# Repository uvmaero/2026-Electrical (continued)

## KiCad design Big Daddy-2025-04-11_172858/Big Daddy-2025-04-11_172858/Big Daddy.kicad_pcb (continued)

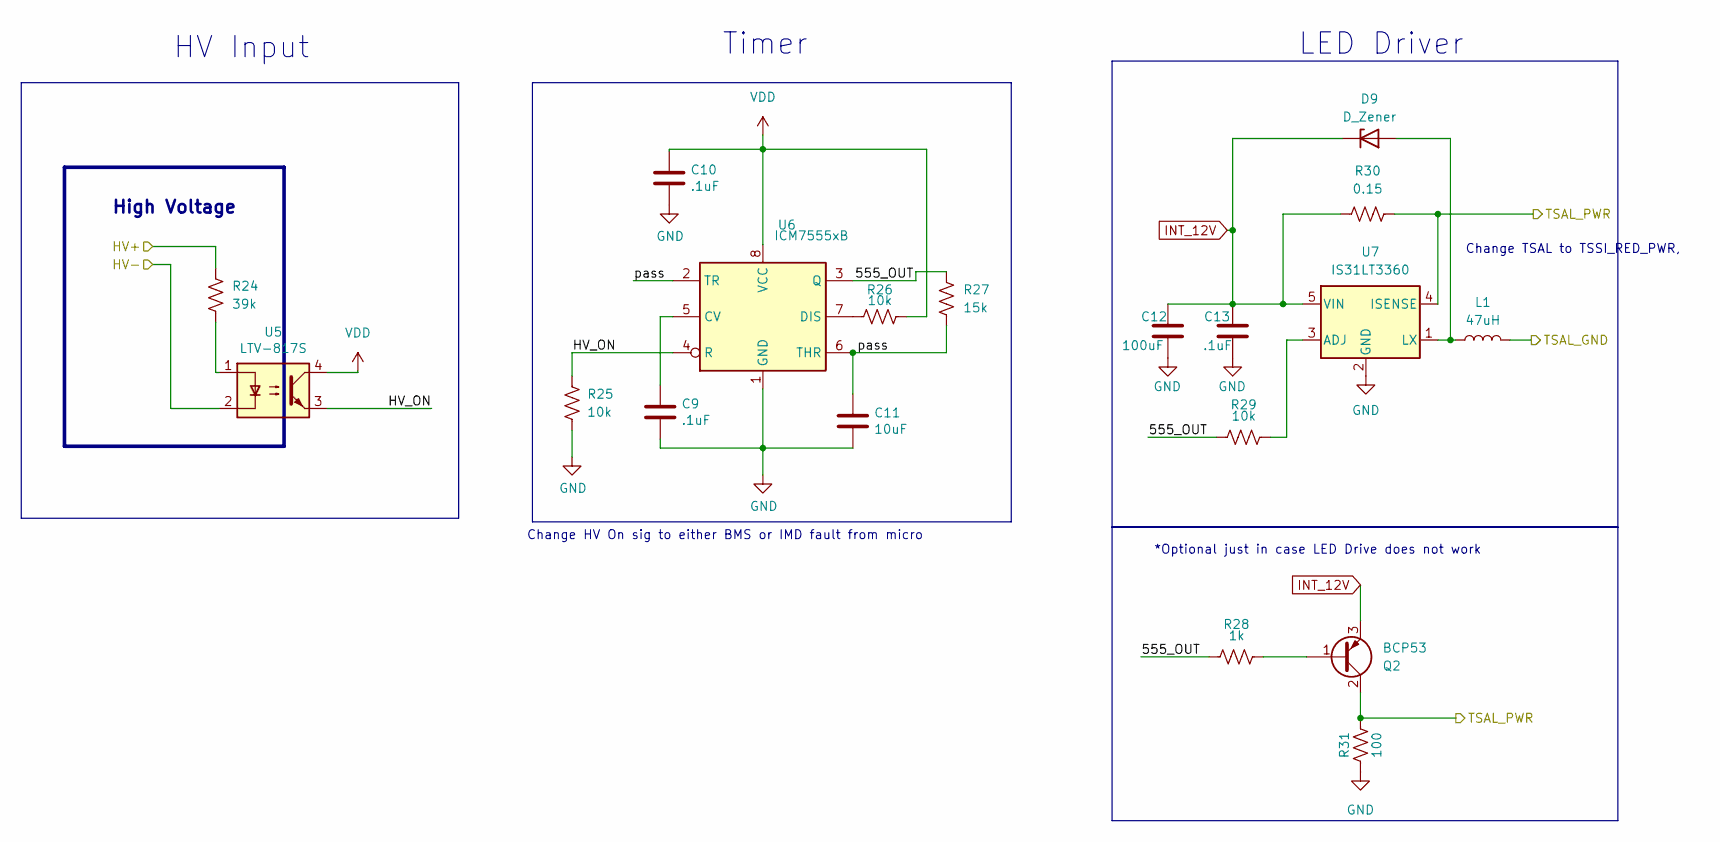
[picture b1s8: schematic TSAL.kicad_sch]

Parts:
C9, C10, C13: .1uF; C_0603_1608Metric_Pad1.08x0.95mm_HandSolder; Manufacturer_Part_Number CC0603KRX7R7BB104; Digikey part number 311-1088-1-ND
C11: 10uF; C_0603_1608Metric_Pad1.08x0.95mm_HandSolder; Manufacturer_Part_Number CL10A106KQ8NNNC; Digikey part number 1276-1038-1-ND
C12: 100uF; CP_Radial_D10.0mm_P5.00mm
D9: D_Zener; D_SOD-123; Manufacturer_Part_Number MMSZ5231B-7-F; Digikey part number MMSZ5231B-FDICT-ND
L1: 47uH; L_0603_1608Metric_Pad1.05x0.95mm_HandSolder; Manufacturer_Part_Number LBMF1608T470K; Digikey part number 587-1716-1-ND
Q2: BCP53; SOT-223-3_TabPin2; Manufacturer_Part_Number BCP53; Digikey part number BCP53FSCT-ND
R24: 39k; R_Axial_DIN0414_L11.9mm_D4.5mm_P15.24mm_Horizontal; Manufacturer_Part_Number CF12JT39K0; Digikey part number CF12JT39K0CT-ND
R25, R26, R29: 10k; R_0603_1608Metric_Pad0.98x0.95mm_HandSolder; Manufacturer_Part_Number RK73H1JTTD1002F; Digikey part number 2019-RK73H1JTTD1002FCT-ND
R27: 15k; R_0603_1608Metric_Pad0.98x0.95mm_HandSolder; Manufacturer_Part_Number ERA-3AEB153V; Digikey part number P15KDBCT-ND
R28: 1k; R_0603_1608Metric_Pad0.98x0.95mm_HandSolder; Manufacturer_Part_Number RMCF0603FT1K00; Digikey part number RMCF0603FT1K00CT-ND
R30: 0.15; R_0603_1608Metric_Pad0.98x0.95mm_HandSolder; Manufacturer_Part_Number RL0603FR-070R15L; Digikey part number 311-.15QCT-ND
R31: 100; R_1206_3216Metric_Pad1.30x1.75mm_HandSolder; Manufacturer_Part_Number ERJ-8ENF1000V; Digikey part number P100FCT-ND
U5: LTV-817S; SMDIP-4_W9.53mm; Manufacturer_Part_Number LTV-817S; Digikey part number 160-1367-5-ND
U6: ICM7555xB; SOIC-8_3.9x4.9mm_P1.27mm; Manufacturer_Part_Number ICM7555CBAZ-T; Digikey part number ICM7555CBAZ-TCT-ND
U7: IS31LT3360; SOT-89-5; Manufacturer_Part_Number IS31LT3360-SDLS4-TR; Digikey part number 2521-IS31LT3360-SDLS4-TRCT-ND

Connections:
/Connectors/TSAL_GND: L1.2; also elsewhere on the board
/Connectors/TSAL_PWR: Q2.2 (C), Q2.4 (C), R30.2, R31.2, U7.4 (ISENSE); also elsewhere on the board
/High Voltage/TSAL/555_OUT: R27.1, R28.1, R29.1, U6.3 (Q)
/High Voltage/TSAL/HV+: R24.1; also elsewhere on the board
/High Voltage/TSAL/HV-: U5.2; also elsewhere on the board
/High Voltage/TSAL/HV_ON: R25.1, U5.3, U6.4 (R)
/High Voltage/TSAL/pass: C11.1, R27.2, U6.2 (TR), U6.6 (THR)
GND: C9.2, C10.2, C11.2, C12.1, C13.1, R25.2, R31.1, U6.1 (GND), U7.2 (GND); also elsewhere on the board
INT_12V: C12.2, C13.2, D9.1 (K), Q2.3 (E), R30.1, U7.5 (VIN); also elsewhere on the board
unnamed: D9.2 (A), L1.1, U7.1 (LX)
unnamed: Q2.1 (B), R28.2
unnamed: R24.2, U5.1
unnamed: C9.1, U6.5 (CV)
unnamed: R26.1, U6.7 (DIS)
unnamed: R29.2, U7.3 (ADJ)
VDD: C10.1, R26.2, U5.4, U6.8 (VCC); also elsewhere on the board

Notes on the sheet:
Change HV On sig to either BMS or IMD fault from micro
*Optional just in case LED Drive does not work
LED Driver
High Voltage
HV Input
Timer
Change TSAL to TSSI_RED_PWR,

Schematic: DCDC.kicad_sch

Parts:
C14, C15: 0.68uF; C_Rect_L18.0mm_W8.0mm_P15.00mm_FKS3_FKP3
C16, C17: 4700uF; C_Radial_D18.0mm_H35.5mm_P7.50mm
L2: 1uH; L_1008_2520Metric_Pad1.43x2.20mm_HandSolder; Manufacturer_Part_Number LQM2HPN1R0MG0L; Digikey part number 490-5112-1-ND
L3: 0.15uH; L_0805_2012Metric_Pad1.15x1.40mm_HandSolder; Manufacturer_Part_Number CE201210-R15J; Digikey part number CE201210-R15JCT-ND
R35, R40: 1; R_2512_6332Metric_Pad1.40x3.35mm_HandSolder; Manufacturer_Part_Number RK73H1JTTD1002F; Digikey part number 2019-RK73H1JTTD1002FCT-ND
R36: 300; R_0603_1608Metric_Pad0.98x0.95mm_HandSolder; Manufacturer_Part_Number ERJ-3GEYJ301V; Digikey part number P300GCT-ND
R37, R38, R39: 1k; R_0603_1608Metric_Pad0.98x0.95mm_HandSolder; Manufacturer_Part_Number RMCF0603FT1K00; Digikey part number RMCF0603FT1K00CT-ND
RV1: 50k TC33x-2-503E; Potentiometer_Bourns_TC33X_Vertical; Manufacturer_Part_Number TC33X-2-503E; Digikey part number TC33X-503ECT-ND
U8: Vicor_AERO; vicor-socket-no-cutouts
U9: LTV-817S; SMDIP-4_W9.53mm; Manufacturer_Part_Number LTV-817S; Digikey part number 160-1367-5-ND
U10: TLP184; MFSOP6-4_4.4x3.6mm_P1.27mm; Manufacturer_Part_Number TLP184(BL-TPL,SE; Digikey part number TLP184(BL-TPLSECT-ND

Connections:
/Fusing/Vicor_In: C17.1, L3.2, R40.1; also elsewhere on the board
/High Voltage/DCDC/EN_HV: U8.3 (EN), U9.4
/High Voltage/DCDC/FAULT_HV: R37.2, U8.4 (FT)
/High Voltage/DCDC/HV+: L2.1, R35.2; also elsewhere on the board
/High Voltage/DCDC/HV-: C14.2, C15.2, RV1.1, U8.5 (-IN), U9.3, U10.3; also elsewhere on the board
/High Voltage/DCDC/TRIM_HV: R36.1, U8.2 (TR)
/High Voltage/Vicor_Enable: R38.1, R39.2; also elsewhere on the board
/High Voltage/Vicor_Fault: U10.6; also elsewhere on the board
GND: C16.2, C17.2, U8.8 (-OUT), U9.2, U10.4; also elsewhere on the board
unnamed: R36.2, RV1.2
unnamed: R37.1, U10.1
unnamed: R38.2, U9.1
unnamed: C14.1, C15.1, L2.2, R35.1, U8.1 (+IN)
unnamed: C16.1, L3.1, R40.2, U8.9 (+OUT)
VDD: R39.1; also elsewhere on the board

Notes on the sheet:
HV Side is pulled high enternally, optoisolator turns on (with high signal) to pull en_hv low
Willem Hillier UVM AERO 3/5/2019
Trim Control
Input Filtering
HV->12V DC-DC
DC/DC out
Output Filtering
HV Danger!
Pull high to disable
500V-rated caps
HV-Interface
FAULT_HV can only supply 4mA absolute max, hence the different optocoupler choice.

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
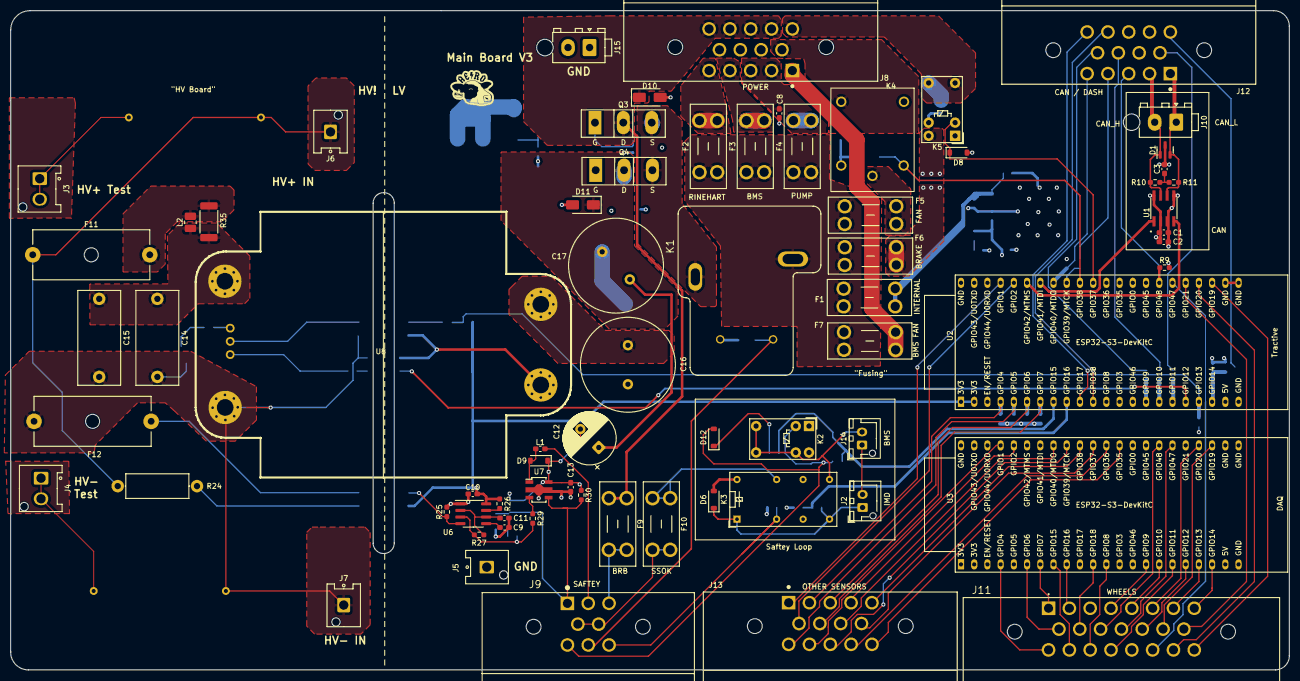
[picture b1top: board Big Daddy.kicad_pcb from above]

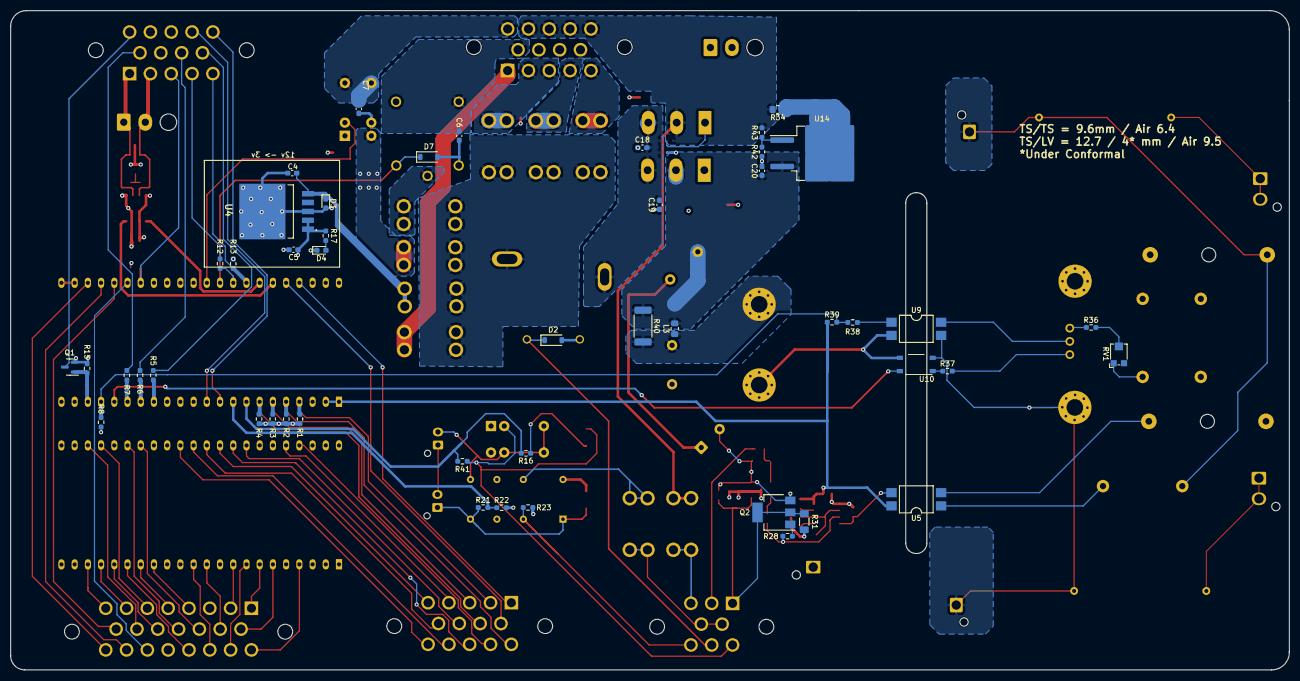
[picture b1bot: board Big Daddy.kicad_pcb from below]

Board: 4 copper layers, 245.6 x 126.6 mm, 119 parts (47 on the bottom side), 112 nets.

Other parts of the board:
R41: 2.2k; R_0603_1608Metric_Pad0.98x0.95mm_HandSolder

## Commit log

2026-03-17 Add files via upload
    Tyler's board from 2025
2026-03-17 fixed HV connections to TSMP and HV-in
2026-03-17 diode arrays deleted
2026-03-18 changed bms relay
2026-03-21 PCB fixes
    BMS relay
    C12 footprint
    TSMP resistor connections
2026-03-24 BMS Indicator
2026-03-24 changed LED connections and logic
2026-03-26 all the bs
2026-03-27 Major TSV components wiring diagram
2026-03-31 Uploaded full TSV wiring schematic file
2026-04-24 new charging circuit
2026-04-24 updated charger
